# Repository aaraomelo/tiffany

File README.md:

# tiffany — o corpo universal

Tudo aqui é um **corpo**, e ele é **autossimilar**: uma peça — o *gato* e o seu *esquilo* — que se
repete em toda escala e dimensão, sem nunca mudar. Dele se derivam a aritmética, a geometria, a
dinâmica e a linguagem. E o que costuma exigir maquinário — a *transformada*, a *convolução*, a
*deconvolução*, a *inversa* — aqui não se constrói: é **propriedade do corpo**, apenas **colhida**.

Cada afirmação é **medida na cifra** (código C puro, sem física nem parâmetro inventado), contra um
oráculo externo, com **resíduo 0** — exata, ou falha.

*Autor: Aarão Melo Lopes.*

## A peça

O gato é a matriz `A_m = [[m,1],[1,0]]` (det = −1). O seu ponto fixo é a **realimentação**:

```
σ = m + 1/σ
```

— σ dos dois lados, o sinal que volta: a raiz de `x²−mx−1`, o **metal** `σ_m` (m=1 ouro φ, m=2 prata,
m=3 bronze). Iterada, a mesma peça é o corpo **Rⁿ = GF(pⁿ)** em qualquer dimensão — a multiplicação é
recursiva, a dimensão `n` vem da `n−1`, o mesmo laço uma volta abaixo.

O gato tem dois atratores **duais**, os dois lados do corpo:

| | atrator | papel | operação |
|---|---|---|---|
| **negro** | `σ`, \|σ\|>1 | sorvedouro — a fala cai | convolução (`×σ`, sobe) |
| **branco** | `σ'=−1/σ`, \|σ'\|<1 | fonte — a resposta emana | deconvolução (`×σ'`, desce) |

com `σσ'=−1` (a mão que segura). O **esquilo** é o dual que traz de volta — e ele não se constrói,
**colhe-se da borda**: de `σⁿ = m·σⁿ⁻¹ + 1` sai `σ⁻¹ = σⁿ⁻¹ − m·σⁿ⁻²`, dois termos da própria
realimentação, sem Fermat e sem eliminação.

## A tese que organiza o resto

Uma **inversão**: a dimensão inteira **não é o objeto** — é um *ponto de ancoragem*. O que existe em
quantidade é o contínuo (os racionais têm medida nula, e quase todo corte é aperiódico), e a dimensão
inteira é onde esse contínuo encosta e trava. **Simetria ancora; deformação é a dinâmica.** E a peça
está *entre* os dois lados do corpo — não é progressão aritmética nem geométrica —, sendo por não
estacionar de nenhum lado que gera corpo em toda dimensão.

Dois corolários que o projeto mede:

- **Os rótulos trocam com a base.** "Inteiro", "racional" e "irracional" não são propriedades do
  número: `1/φ` é irracional em ℚ e é `(−1,1)` — inteiro — em `ℤ[σ]`. Cada dimensão é um irracional
  que **colapsa em inteiro** na passagem.
- **A assimetria que basta é a *anti*ssimétrica.** Sem assimetria não há nada — e a forma
  `ω(u,v) = −ω(v,u)` é a única que existe do mesmo modo em **toda** dimensão: uma só classe sempre
  (contra `≥2` da simétrica em `F_p`, `n+1` em `R`), zero em dimensão ímpar, e `nula` em `n=1`. Ela é
  `0` sobre um ponto e não-degenerada sobre pares — *carrega tudo e nada*: não mede ponto, mede
  **diferença**. Em `n=2` ela **é** `ℂ` (`J²=−I`), e dela sai a lei de potência (`det = Pf²`, módulo
  `|x|^d`).
- **π é o `0`.** *Ciclotomia* significa "corte do círculo": dividir o círculo em `n` devolve o centro
  (`Σζⁿ = 0`), e o circuito fecha (`ζⁿ=1`). Os metais são de π exatamente (`1/φ = 2cos(2π/5)`), e o
  que π alcança é a extensão **abeliana máxima** — o que fica fora é o não-abeliano, e o exemplo é o
  fator plástico do furo do ouro na dimensão 5.

## Os três papers

| paper | o quê |
|---|---|
| `teoria.tex` | **O Alfabeto e a Operação** — o corpo autossimilar `Rⁿ`, os rótulos e o gerador, as progressões, a dualidade, a deformação e o AGM, a colheita |
| `microprocessador.tex` | **o gabarito** — o circuito analógico, a peça translinear `ANTILOG(log a + s·log b − s·log ref)` (`s=+1` gato, `s=−1` esquilo), o gerador global, os terminais onde se colhe |
| `tiffany.tex` | **a fala** — a assistente: o corpus é um grafo de órbitas, a fala cai nele, e o caminho que passa por ela é a resposta; e o §6, onde a tradução por *embedding* exato **não fecha**, com a causa contada |

O `teoria.tex` está em sete seções: **§1** a peça · **§2** os rótulos e o gerador · **§3** as duas
progressões e o dupolinômio · **§4** o corpo `Rⁿ` · **§5** a dualidade · **§6** a dimensão é ancoragem
· **§7** a colheita.

## A cifra — o código

Em `tools/`, cada arquivo mede uma afirmação e devolve **resíduo 0**. C puro (libc + libm):

```
cc -O2 tools/checkup.c -lm -o /tmp/checkup && /tmp/checkup
```

Para rodar **tudo**: a bateria extrai a lista dos próprios papers, compila e roda cada medidor sob teto
de memória e `timeout`:

```
./tools/bateria.sh
```

**59 medidores — 57 verdes, 2 negativos por projeto, 0 falhas.** Os dois negativos
(`tatoeba/ancora.c`, `tatoeba/homogeneo.c`) devolvem `1` porque *provam* que o sistema da tradução não
tem solução — é resultado, não quebra.

A peça vive **uma vez** em cada header e é reusada por `#include` — a auto-similaridade posta no próprio
código: `gp2.h` (GF(p²)), `gf2n.h` (GF(2ⁿ)), `quat.h` (ℍ=M₂), `pgm.h` (imagens). O índice completo, seção
por seção, está em [`tools/LEIAME.md`](tools/LEIAME.md).

### O gerador, e por que ele vai escrito

O gerador não é invenção deste projeto — é o do **corpo universal**, e basta recolhê-lo: um primo `p` com
`n | p−1`, o **menor** gerador `g`, a torção `w = g^((p−1)/n)` (cuja órbita *é* a base, que portanto não
se escolhe) e a normalização `r² = n`. Para texto em bytes: `p=40961, g=3, w=36043, r=16`.

A única propriedade que a construção usa é `χ_k(u+v) = χ_k(u)·χ_k(v)` — o caractere leva `⊕` a `⊗` — e a
torção **basta** porque o dual do dual devolve o grupo: as inversas (da transformada, da convolução, o
flip) são consequências de **uma** razão, não três teoremas. E há **um** gerador, com projeções
encadeadas `w_d = g^((p−1)/d)`, que se abrem de baixo nas ordens que a necessidade pede.

### O neurônio, e o AGM — a mesma peça em dois meios

`tools/neuronio.c` (bits) e `tools/neuronio_analog.c` (correntes) são a **mesma peça** em dois meios: o
sinal parte em fases (`⊕`), soma-se cada uma (`∑`, Kirchhoff) e o gato sobe a torre — temporal (`Aᵏ`, a
razão → `σ_m`) e dimensional (`Aₙ` em `R²⊂R³⊂⋯`) —, o esquilo desce. Os dois dão o mesmo resultado
(`tools/fractal.c`, resíduo 0). *O bit era a amputação, o corpo é a onda.*

O mesmo vale para o **AGM**, que é a tríade batendo alternada (`⊕` e `⊗`) e cujo invariante é uma
integral: `tools/agm.c` (exato) e `tools/agm_analog.c` (colhido no circuito, onde a média geométrica é o
translinear com somador em ganho ½ — e **dispensa a corrente de referência**). E a sua dinâmica **é** a
do gerador: conjugado por `h : k ↦ τ = K′/K`, o AGM é `τ ↦ 2τ`, e a torre da torção é `w_d = (w_{2d})²`
— nos dois lados, a multiplicação por 2 no grupo (`tools/agm_gerador.c`).

## Estrutura

```
teoria.tex · tiffany.tex · microprocessador.tex   os três papers
tools/       a cifra (.c + .h) e bateria.sh — tudo resíduo 0 ou falha
tatoeba/     o pipeline da assistente sobre o corpus Tatoeba
hardware/    a placa so_cristal (Gerbers, KiCad, DRC 0 violações)
```

Os PDFs dos papers e os binários compilados são regenerados localmente (ver `.gitignore`); os dados
grandes do corpus (`tatoeba/*.tsv`) não são versionados.

---

> *"Não se implementa a matemática; colhe-se o que o circuito, sendo o corpo, já faz."*

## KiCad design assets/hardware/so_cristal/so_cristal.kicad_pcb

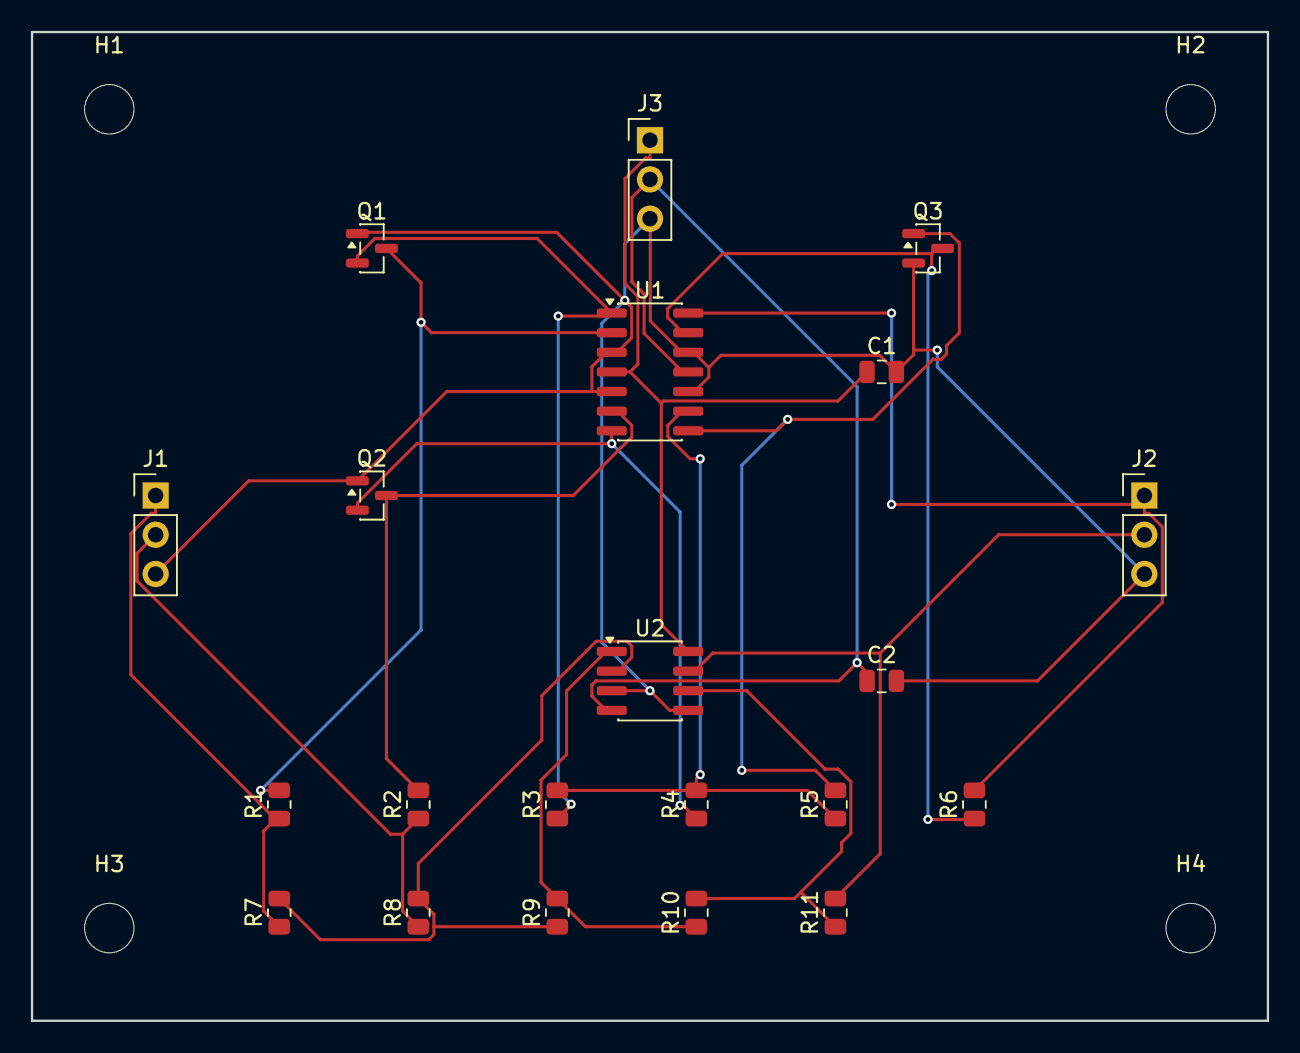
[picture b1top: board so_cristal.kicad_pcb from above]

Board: 2 copper layers, 80.0 x 64.0 mm, 25 parts (0 on the bottom side), 17 nets.

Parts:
C1, C2: 100nF; C_0805_2012Metric
H1, H2, H3, H4: MountingHole_3.2mm_M3
J1: IN a b G; PinHeader_1x03_P2.54mm_Vertical
J2: OUT M A G; PinHeader_1x03_P2.54mm_Vertical
J3: V+ V- G; PinHeader_1x03_P2.54mm_Vertical
Q1, Q2, Q3: MMBT3904; SOT-23
R1, R2, R3, R4, R5, R6, R7, R8, R9, R10, R11: 100k; R_0805_2012Metric
U1: TL074; SOIC-14_3.9x8.7mm_P1.27mm
U2: TL072; SOIC-8_3.9x4.9mm_P1.27mm

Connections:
ADD: J2.2, R11.2, U2.7
ADDN: R9.2, R10.1, U2.1
A_in: J1.1, R1.1, R7.1
B_in: J1.2, R2.1, R8.1
GND: C1.2, C2.2, J1.3, J2.3, J3.3, Q1.1, Q2.1, Q3.2, U1.3, U1.5, U1.10, U1.12, U2.3, U2.5
LOGA: Q1.2, R3.1, U1.1
LOGB: Q2.2, R4.1, U1.7
MULT: J2.1, R6.2, U1.14
SUMV: Q3.1, R5.2, U1.8
VCC: C1.1, J3.1, U1.4, U2.8
VEE: C2.1, J3.2, U1.11, U2.4
n1: Q1.3, R1.2, U1.2
n2: Q2.3, R2.2, U1.6
n3: R3.2, R4.2, R5.1, U1.9
n4: Q3.3, R6.1, U1.13
n5: R7.2, R8.2, R9.1, U2.2
n6: R10.2, R11.1, U2.6
